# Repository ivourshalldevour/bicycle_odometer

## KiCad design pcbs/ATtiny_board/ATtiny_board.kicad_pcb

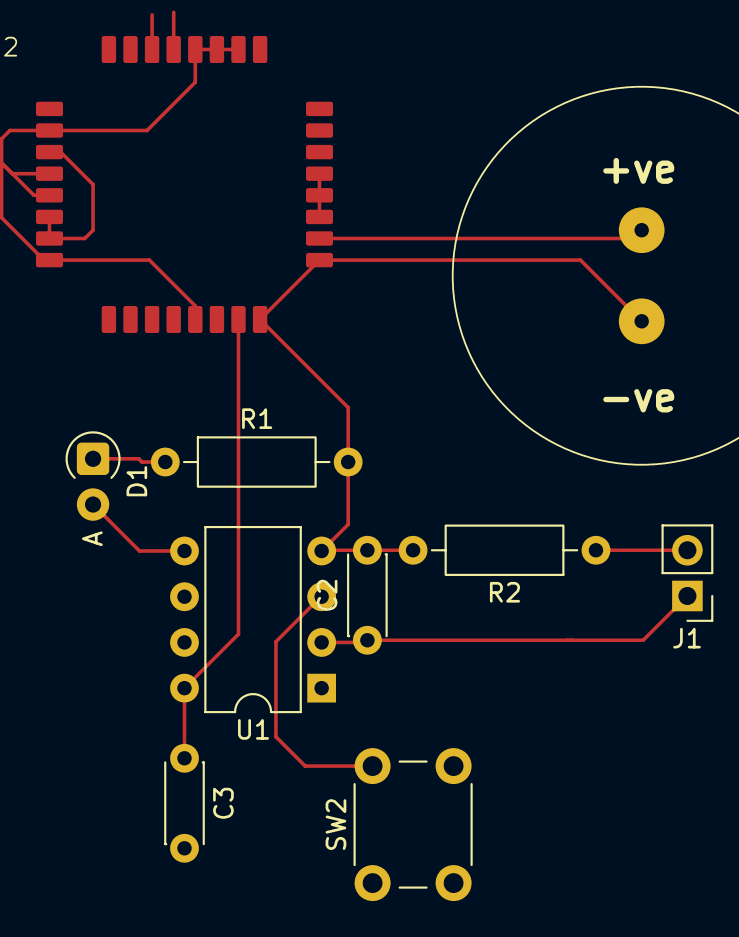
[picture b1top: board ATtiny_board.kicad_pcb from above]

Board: 2 copper layers, 11 parts (0 on the bottom side), 15 nets.

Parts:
C1: 1F 5.5V; 1FSuperCap
C2: 440μF; C_Disc_D4.3mm_W1.9mm_P5.00mm
C3: 0.1μF; C_Disc_D4.3mm_W1.9mm_P5.00mm
D1: LED; D_A-405_P2.54mm_Vertical_AnodeUp
J1: To reedswitch; PinHeader_1x02_P2.54mm_Vertical
R1: 330Ω; R_Axial_DIN0207_L6.3mm_D2.5mm_P10.16mm_Horizontal
R2: 1.8kΩ; R_Axial_DIN0207_L6.3mm_D2.5mm_P10.16mm_Horizontal
SC1: KXOB25-05X3F
SW2: Display Switch; SW_PUSH_6mm
U1: ATtiny85V-10PU; DIP-8_W7.62mm
U2: AEM10941_board

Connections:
unnamed: D1.2 (A), U1.5 (AREF/PB0)
unnamed: D1.1 (K), R1.1
unnamed: C2.1, J1.1, U1.2 (XTAL1/PB3)
unnamed: J1.2, R2.1
unnamed: SC1.1 (+), U2.29 (SRC)
unnamed: SC1.2 (-), U2.30 (GND)
unnamed: C1.2, C2.2, C3.2, R1.2, R2.2, SW2.2, U1.4 (GND), U2.16 (GND), U2.17 (BAL)
unnamed: U1.6 (PB1), U2.23 (STATUS[1])
unnamed: C3.1, U1.8 (VCC), U2.15 (HVOUT)
unnamed: SW2.1, U1.3 (XTAL2/PB4)
unnamed: C1.1, U2.18 (BAT)
unnamed: U2.2 (BUCK), U2.4 (CFG1), U2.5 (CFG0), U2.8 (SELMPP[0]), U2.13 (ENHV), U2.26 (SET_OVCH), U2.27 (SET_CHRDY), U2.28 (SET_OVDIS)
unnamed: U2.3 (CFG2), U2.6 (GND), U2.7 (SELMPP[1])
unnamed: U2.19 (PRIM), U2.20 (ENLV), U2.21 (GND)
unnamed: U2.9 (FB_PRIM_D), U2.10 (FB_PRIM_U), U2.11 (GND)

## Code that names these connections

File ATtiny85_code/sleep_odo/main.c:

/*
    This code makes the ATtiny85 count falling edges casued by a reed switch
    connected to PB3 (pin 2). A falling edge triggers an interrrupt which makes
    the main program loop increase the wheel revolution count in SRAM.

    It will display the wheel count by flashing an LED (on pin 5) that many
    times when a button connected to PB4 (pin 3) is pressed.

    A rising edge on pin 6 (PCINT1) triggers the wheel revolution count stored
    in SRAM to be written permanently to EEPROM. 

    Uses default internal 8MHz osc with divide-by-8 prescaler to make 1MHz
    clock signal.

    Assumes reed switch is hardware debounced with a 1uF capacitor. Assumes
    pin6 is pulled-down by power supply unit digital output. Because it is a
    digital input from a digital output, no debouncing needed. If using a
    mechanical switch during testing, make sure to debounce pin6 with cap.
*/

#define F_CPU 1000000UL // used for util/delay.h
#include <avr/eeprom.h>
#include <avr/io.h>
#include <avr/interrupt.h>
#include <avr/sleep.h>
#include <util/delay.h>

// Globals used as flags by interrupt service routines
uint8_t odo_interrupt = 0;      // when another wheel revolution happens
uint8_t disp_interrupt = 0;     // when someone wants to read the odometer count
uint8_t save_interrupt = 0;     // save odo_count to eeprom when pin 6 goes high
uint32_t temp_odo = 0;          // temporary count of wheel rotations stored in SRAM
#define ODO_ADDR 0 // address of odo_count variable

// Helper functions
void doubleDabble();



int main() {
    cli();    // disable interrupts during setup

    DDRB  = 0x00;   // Set all pins to be inputs.
    PORTB = 0xFF;   // Pull-up resistors enabled.

    // Set PB0 (pin 5) as output for LED
    PORTB = PORTB & 0b11111110; // disable pull-up and output LOW
    DDRB = DDRB | (1<<PINB0);   // direction to output
    // disable pull-up on pin6 PB1
    PORTB &= 0b11111101;

    // clear pin change interrupt flag
    GIFR = 1 << PCIF; // done by writing a 1 (yes weird).

    // Set PB4, PB3 & PB1 as pin-change interrupt capable.
    GIMSK = 1 << PCIE; // enable pin-change interrupts
    PCMSK = (1 << PCINT4) | (1 << PCINT3) | (1 << PCINT1); // Mask for only PB4, PB3 & PB1

    // set sleep mode to powerdown
    MCUCR = (MCUCR & ~((1<<SM1) | (1<<SM0))) | (1<<SM1);

    // Disable Timer1, USI and ADC
    PRR = (1<<PRTIM1) | (1<<PRUSI) | (1<< PRADC);

    sei();    // Enable interrupts in status register


    for(;;) {
        // Reed switch from rotating wheel was triggered so increase temp_odo
        if(odo_interrupt) {
            temp_odo++;
            odo_interrupt = 0;
        }
        
        
        // display odo_count stored in eeprom
        if(disp_interrupt) {
            uint32_t odo_count;
            eeprom_read_block(&odo_count, ODO_ADDR, 4);  // get wheel revs
            uint8_t bcd[10]; // 32bit converts to 10 decimal digits
            doubleDabble(bcd, odo_count); // convert odo_count to BCD
            
            // now blink LED that many times as each BCD digit.
            uint8_t i = 0;
            uint8_t j = 0;
            /*
            	// blinks in BCD but doesnt skip leading zeros
            for(i=0; i<10; i++) {
                uint8_t blink_times = bcd[i];
                if(blink_times == 0) {
                    PORTB = PORTB | (1<<PINB0); // on
                    _delay_ms(750);
                    PORTB = PORTB & ~(1<<PINB0);    // off
                    _delay_ms(250);
                }
                for(j=0;j<blink_times; j++) {
                    PORTB = PORTB | (1<<PINB0); // on
                    _delay_ms(250);
                    PORTB = PORTB & ~(1<<PINB0);    // off
                    _delay_ms(250);
                }
                _delay_ms(250); // delay between digits
            }*/
            // blinks in BCD, skipping leading zeros
            while((i<10) && (bcd[i] == 0)) i++; // go to first non-zero digit
            if(i==10) { // all digits were zero. Still need to display 0.
                PORTB = PORTB | (1<<PINB0); // on
                _delay_ms(1000);
                PORTB = PORTB & ~(1<<PINB0);    // off
            }
            while(i<10) {   // blink for all digits onwards
                uint8_t blink_times = bcd[i];
                if(blink_times == 0) {  // long blink for zero
                    PORTB = PORTB | (1<<PINB0); // on
                    _delay_ms(1000);
                    PORTB = PORTB & ~(1<<PINB0);    // off
                    _delay_ms(250);
                }
                for(j=0; j<blink_times; j++) {
                    PORTB = PORTB | (1<<PINB0); // on
                    _delay_ms(250);
                    PORTB = PORTB & ~(1<<PINB0);    // off
                    _delay_ms(250);
                }
                _delay_ms(500); //delay between digits
                i++;
            }
			
            /*
            // blinks LED the raw ammount of times stored in odo_count (only while button held)
            for(uint32_t i=0; i<odo_count; i++) {   // blink LED that many times
                if((PINB & (1<<PINB4)) != 0) break;  // Stop looping if button is released.
                PORTB = PORTB | (1<<PINB0); // set HIGH
                _delay_ms(250);
                PORTB = PORTB & ~(1<<PINB0);    // set LOW
                _delay_ms(250);
            }*/
            disp_interrupt = 0;
        }
        
        
        // save temp_odo to eeprom when pin 6 goes high
        if(save_interrupt) {
            if(temp_odo != 0) {    // only save if there are new counts
                uint32_t odo_count;
                eeprom_read_block(&odo_count, ODO_ADDR, 4); // read 4 bytes
                odo_count = odo_count + temp_odo;
                temp_odo = 0;   // clear the tally
                eeprom_write_block(&odo_count, ODO_ADDR, 4);    // write 4 bytes
            }
            save_interrupt = 0;
        }


        // go to sleep
        MCUCR |= (1<<SE);   // sleep enable
        __asm__ __volatile__ ("sleep"); // volatile so it doesnt get compiled away

        // CPU will resume here after being woken from sleep
        MCUCR &= ~(1<<SE);  // clear sleep enable
    }

    return 0;
}




// Interrupt service routine for a pin change on either PB3,PB4, or PB1.
ISR(PCINT0_vect) {
    // MCUCR &= ~(1<<SE);  // clear sleep enable

    // check which pin caused the interrupt
    if((PINB & (1<<PINB3)) == 0) {    // active low
        odo_interrupt = 1;
    }
    else if ((PINB & (1<<PINB1)) != 0) {    // active high
        save_interrupt = 1;
    }
    else if((PINB & (1<<PINB4)) == 0) {   // active low
        disp_interrupt = 1;
    }
    
    // keep in mind that this interrupt routine will be triggered for both
    // rising and falling edges of the signals on PB4, PB3 & PB1. It is
    // assumed the inputs are well debounced and sufficiently long to stay in
    // the same state during the interrupt service. If the pin is still LOW it
    // was a falling edge. If the pin is read HIGH, it was a rising edge.   `
}


/*
    Converts 32bit binary into 10 digit BCD. The BCD only takes up 5 bytes,
    because each byte stores two BCD digits. (1 BCD digit is 4bits).
*/
void doubleDabble(uint8_t bcd[10], uint32_t binary) {
    uint8_t scratch[5] = {0,0,0,0,0};   // scratch space
    uint8_t i,j;
    uint8_t carry;
    
    // 32 iterations
    for(i=0; i<32; i++) {
        // check all BCD digits if above 4
        for(j=0; j<5; j++) {    // each scratch[i] contains two BCD digits
            if((scratch[j] & 0xF0) > 0x40) {  // check high digit first
                scratch[j] += 0x30; // plus 3 to high digit
            }
            if((scratch[j] & 0x0F) > 0x04) { // now check low digit
                scratch[j] += 0x03; // plus 3 to low digit
            }
        }
        
        // left shift everything
        carry = (binary & (0b1UL<<31)) ? 1 : 0;   // carry=1 if MSB of binary is 1
        binary <<= 1;
        for(j=5; (j--)>0; ) {
            uint8_t new_carry = (scratch[j] & 0x80) ? 1 : 0;
            scratch[j] <<= 1;
            scratch[j] |= carry;
            carry = new_carry;
        }
    }
    
    // unpack the BCD digits from scratch space.
    bcd[0] = scratch[0] >> 4;       // upper nibble
    bcd[1] = scratch[0] & 0x0F;     // lower nibble
    bcd[2] = scratch[1] >> 4;
    bcd[3] = scratch[1] & 0x0F;     // etc...
    bcd[4] = scratch[2] >> 4;
    bcd[5] = scratch[2] & 0x0F;
    bcd[6] = scratch[3] >> 4;
    bcd[7] = scratch[3] & 0x0F;
    bcd[8] = scratch[4] >> 4;
    bcd[9] = scratch[4] & 0x0F;
}

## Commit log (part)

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2025-03-24 Added datasheet and gitignore
2025-03-24 First bit of code for MSP430, doesn't work yet.
2025-03-25 Got LED to turn on with button
2025-04-07 Added testing data collected from coil and magnet
2025-04-07 Sepparated into ATtiny code and msp430 code
2025-04-25 nosleep_odo added to ATtiny code
2025-04-26 Added sleep_odo. Gave up on trying to implement software debouncing, uses hardware debounce.
2025-04-30 Figured out sleeping issue on ATtiny85
2025-05-06 Converted sleep_odo to not use arduino.h
2025-05-27 Added eeprom save triggered by pin 6 for sleep_odo, not tested yet
2025-05-27 Tested sleep_odo with save feature. Works well. Make sure to debounce pin6
2025-05-27 changed gitignore
2025-05-31 Changed order of ISR if statements
2025-07-12 Added logic analyser
2025-07-12 Started i2c slave functionality for ATtiny
2026-05-13 Modified makefile for linux usage
2026-05-18 Removed forced -b19200 option from makefiles avrdude command
2026-05-18 Modified makefile so that it works always in linux
2026-05-18 Programmer works in linux! yay
2026-05-25 Wrote and tested BCD display code
2026-05-26 Started pcb design for ATtiny85
2026-05-28 Designing PCB
2026-05-29 Continued PCB
2026-06-22 added comments to sleep_odo
